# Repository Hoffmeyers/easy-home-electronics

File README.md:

This KiCad project showcases the design of a smart switch system built around the ESP32 microcontroller, aimed at enhancing automation and energy monitoring in residential or commercial settings. The system integrates both 5V and 3.3V low-dropout (LDO) voltage regulators to ensure stable power delivery to the ESP32 and associated components. An AC-DC converter is used to step down and convert mains voltage into usable DC power, making the switch compatible with standard household wiring. Additionally, the circuit incorporates voltage and current sensors to enable real-time power consumption monitoring, allowing users to track energy usage and implement protective features. The layout is optimized for compactness and reliability, with clear signal routing and robust power distribution.

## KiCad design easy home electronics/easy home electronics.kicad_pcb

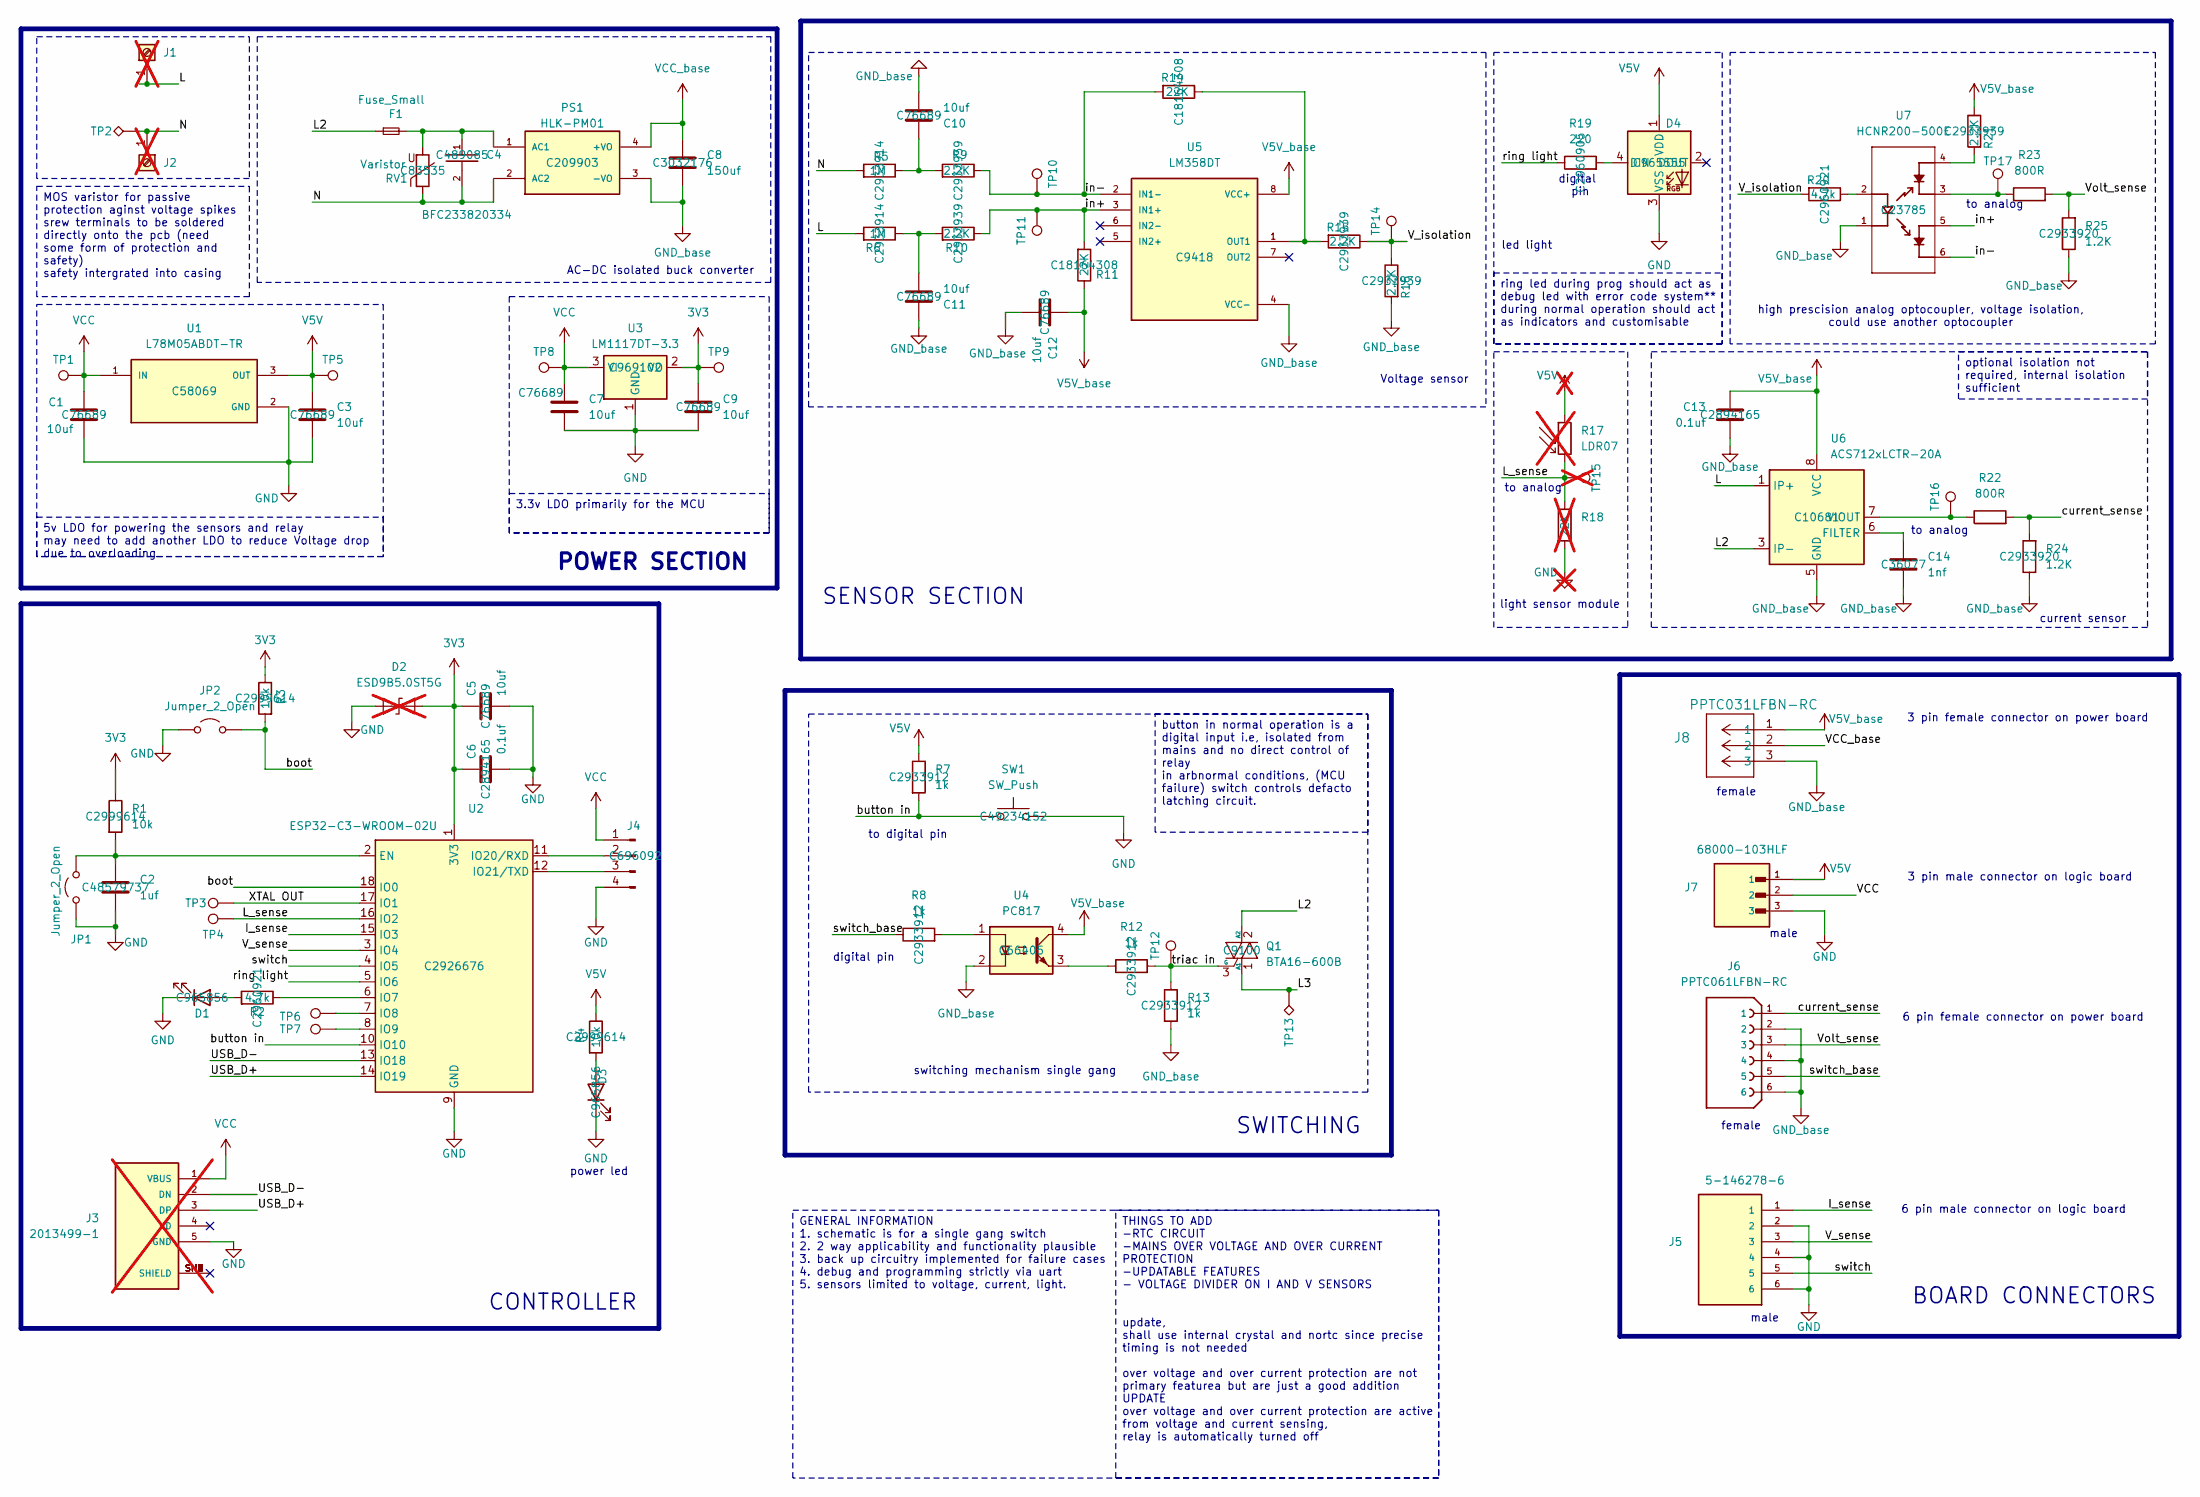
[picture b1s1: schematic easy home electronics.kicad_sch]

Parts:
C1, C3, C5, C7, C9, C10, C11, C12: 10uf; C_1812_4532Metric; LCSC PART NUMBER C76689
C2: 1uf; C_1812_4532Metric; LCSC PART NUMBER C48579737
C4: BFC233820334; CAPRR1500W80L1750T850H1500P; LCSC PART NUMBER C489085
C6, C13: 0.1uf; C_1812_4532Metric; LCSC PART NUMBER C2894165
C8: 150uf; C_Elec_6.3x7.7; LCSC PART NUMBER C3032176
C14: 1nf; C_1812_4532Metric; LCSC PART NUMBER C36077
D1, D3: LED; LED_1206_3216Metric; LCSC PART NUMBER C965856
D2: ESD9B5.0ST5G; D_SOD-923; not fitted
D4: WS2812B; LED_WS2812B_PLCC4_5.0x5.0mm_P3.2mm; LCSC PART NUMBER C965555
F1: Fuse_Small; Fuse_2512_6332Metric
J1, J2: Screw_Terminal_01x01; MountingHole_3mm_Pad_Via; not fitted
J3: 2013499-1; TE_2013499-1; PARTREV B5; not fitted
J4: Conn_01x04_Pin; Molex_PicoBlade_53261-0471_1x04-1MP_P1.25mm_Horizontal; LCSC PART NUMBER C696092
J5: 5-146278-6; TE_5-146278-6; PARTREV R
J6: PPTC061LFBN-RC; SULLINS_PPTC061LFBN-RC; PARTREV L
J7: 68000-103HLF; AMPHENOL_68000-103HLF; PARTREV DG
J8: PPTC031LFBN-RC; CONN_PPTC031_SUL
JP1, JP2: Jumper_2_Open; SolderJumper-2_P1.3mm_Open_TrianglePad1.0x1.5mm
PS1: HLK-PM01; CONV_HLK-PM01; LCSC PART NUMBER C209903
Q1: BTA16-600B; TO-220-3_Vertical; LCSC PART NUMBER C9100
R1, R3, R4: 10k; R_1812_4532Metric_Pad1.30x3.40mm_HandSolder; LCSC PART NUMBER C2999614
R2, R20: 4.7k; R_1812_4532Metric_Pad1.30x3.40mm_HandSolder; LCSC PART NUMBER C2960921
R5, R6: 1M; R_1812_4532Metric_Pad1.30x3.40mm_HandSolder; LCSC PART NUMBER C2933914
R7, R8, R12, R13: 1k; R_1812_4532Metric_Pad1.30x3.40mm_HandSolder; LCSC PART NUMBER C2933912
R9, R10, R15, R16, R21: 2.2K; R_1812_4532Metric_Pad1.30x3.40mm_HandSolder; LCSC PART NUMBER C2933939
R11, R14: 22K; R_1812_4532Metric_Pad1.30x3.40mm_HandSolder; LCSC PART NUMBER C18164308
R17: LDR07; R_LDR_5.1x4.3mm_P3.4mm_Vertical; not fitted
R18: 22K; R_1812_4532Metric_Pad1.30x3.40mm_HandSolder; not fitted
R19: 220; R_1812_4532Metric_Pad1.30x3.40mm_HandSolder; LCSC PART NUMBER C2960905
R22, R23: 800R; R_1812_4532Metric_Pad1.30x3.40mm_HandSolder
R24, R25: 1.2K; R_1812_4532Metric_Pad1.30x3.40mm_HandSolder; LCSC PART NUMBER C2933920
RV1: Varistor; RV_Disc_D12mm_W3.9mm_P7.5mm; LCSC PART NUMBER C83535
SW1: SW_Push; SW_PUSH_6mm_H5mm; LCSC PART NUMBER C49234152
TP1, TP3, TP4, TP5, TP6, TP7, TP8, TP9, TP10, TP11, TP12, TP14, TP16, TP17: TestPoint; TestPoint_Pad_D2.5mm
TP2, TP13: TestPoint_Alt; TestPoint_Pad_4.0x4.0mm
TP15: TestPoint; TestPoint_Pad_D4.0mm; not fitted
U1: L78M05ABDT-TR; VREG_L78M05ABDT-TR; PARTREV 23; LCSC PART NUMBER C58069
U2: ESP32-C3-WROOM-02U; LCSC PART NUMBER C2926676
U3: LM1117DT-3.3; TO-252-3_TabPin2; LCSC PART NUMBER C969102
U4: PC817; DIP-4_W7.62mm; LCSC PART NUMBER C66405
U5: LM358DT; SOIC127P600X175-8N; LCSC PART NUMBER C9418
U6: ACS712xLCTR-20A; SOIC-8_3.9x4.9mm_P1.27mm; LCSC PART NUMBER C10681
U7: HCNR200-500E; OPTO_HCNR200-500E; LCSC PART NUMBER C23785

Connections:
3V3: C5.1, C6.1, C9.1, D2.2 (A2), R1.1, R3.1, TP9.1, U2.1 (3V3), U3.2 (VO)
/I_sense: J5.1, U2.15 (IO3)
/L: J1.1, R6.2, U6.1 (IP+), U6.2 (IP+)
/L2: F1.1, Q1.2 (A2), U6.3 (IP-), U6.4 (IP-)
/L3: Q1.1 (A1), TP13.1
/L_sense: R17.2, R18.1, TP4.1, TP15.1, U2.16 (IO2)
/N: C4.2, J2.1, PS1.2 (AC2), R5.2, RV1.1, TP2.1
/USB_D+: J3.3 (DP), U2.14 (IO19)
/USB_D-: J3.2 (DN), U2.13 (IO18)
/V_isolation: R15.1, R16.1, R20.2, TP14.1
/V_sense: J5.3, U2.3 (IO4)
/Volt_sense: J6.3, R23.2, R25.2
/XTAL OUT: TP3.1, U2.17 (IO1)
/boot: JP2.2 (B), R3.2, U2.18 (IO0)
/button in: R7.2, SW1.1, U2.10 (IO10)
/current_sense: J6.1, R22.2, R24.2
/in+: R10.1, R11.2, TP11.1, U5.3 (IN1+), U7.5
/in-: R9.1, R14.2, TP10.1, U5.2 (IN1-), U7.6
/ring light: R19.1, U2.5 (IO6)
/switch: J5.5, U2.4 (IO5)
/switch_base: J6.5, R8.1
/triac in: Q1.3 (G), R12.2, R13.1, TP12.1
GND: C1.2, C2.2, C3.2, C5.2, C6.2, C7.2, C9.2, D1.1 (K), D2.1 (A1), D3.1 (K), D4.3 (VSS), J3.5 (GND), J4.4, J5.2, J5.4, J5.6, J7.3, JP1.1 (A), JP2.1 (A), R18.2, SW1.2, U1.2 (GND), U2.9 (GND), U2.19 (GND), U3.1 (GND)
GND_base: C8.2, C10.2, C11.1, C12.2, C13.2, C14.2, J6.2, J6.4, J6.6, J8.3, PS1.3 (-VO), R13.2, R16.2, R24.1, R25.1, U4.2, U5.4 (VCC-), U6.5 (GND), U7.1
unnamed: C10.1, R5.1, R9.2
unnamed: C11.2, R6.1, R10.2
unnamed: D1.2 (A), R2.2
unnamed: D3.2 (A), R4.2
unnamed: D4.4 (DIN), R19.2
unnamed: J4.2, U2.11 (IO20/RXD)
unnamed: J4.3, U2.12 (IO21/TXD)
unnamed: C2.1, JP1.2 (B), R1.2, U2.2 (EN)
unnamed: C4.1, F1.2, PS1.1 (AC1), RV1.2
unnamed: R8.2, U4.1
unnamed: R12.1, U4.3
unnamed: R20.1, U7.2
unnamed: R21.2, U7.4
unnamed: R23.1, TP17.1, U7.3
unnamed: R2.1, U2.6 (IO7)
unnamed: TP6.1, U2.7 (IO8)
unnamed: TP7.1, U2.8 (IO9)
unnamed: R14.1, R15.2, U5.1 (OUT1)
unnamed: C14.1, U6.6 (FILTER)
unnamed: R22.1, TP16.1, U6.7 (VIOUT)
V5V: C3.1, D4.1 (VDD), J7.1, R4.1, R7.1, R17.1, TP5.1, U1.3 (OUT)
V5V_base: C12.1, C13.1, J8.1, R11.1, R21.1, U4.4, U5.8 (VCC+), U6.8 (VCC)
VCC: C1.1, C7.1, J3.1 (VBUS), J4.1, J7.2, TP1.1, TP8.1, U1.1 (IN), U3.3 (VI)
VCC_base: C8.1, J8.2, PS1.4 (+VO)

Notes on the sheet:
power led
high prescision analog optocoupler, voltage isolation, could use another optocoupler
led light
current sensor
3 pin male connector on logic board
light sensor module
male
to analog
SENSOR SECTION
digital pin
3 pin female connector on power board
CONTROLLER
BOARD CONNECTORS
SWITCHING
switching mechanism single gang
Voltage sensor
digital pin
6 pin male connector on logic board
female
to digital pin
6 pin female connector on power board
AC-DC isolated buck converter
POWER SECTION
optional isolation not required, internal isolation sufficient
THINGS TO ADD -RTC CIRCUIT -MAINS OVER VOLTAGE AND OVER CURRENT PROTECTION -UPDATABLE FEATURES - VOLTAGE DIVIDER ON I AND V SENSORS update, shall use internal crystal and nortc since precise timing is not needed over voltage and over current protection are not primary featurea but are just a good a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
MOS varistor for passive protection aginst voltage spikes srew terminals to be soldered directly onto the pcb (need some form of protection and safety) safety intergrated into casing
GENERAL INFORMATION 1. schematic is for a single gang switch 2. 2 way applicability and functionality plausible 3. back up circuitry implemented for failure cases 4. debug and programming strictly via uart 5. sensors limited to voltage, current, light.
3.3v LDO primarily for the MCU
button in normal operation is a digital input i.e, isolated from mains and no direct control of relay in arbnormal conditions, (MCU failure) switch controls defacto latching circuit.
ring led during prog should act as debug led with error code system** during normal operation should act as indicators and customisable
5v LDO for powering the sensors and relay may need to add another LDO to reduce Voltage drop due to overloading

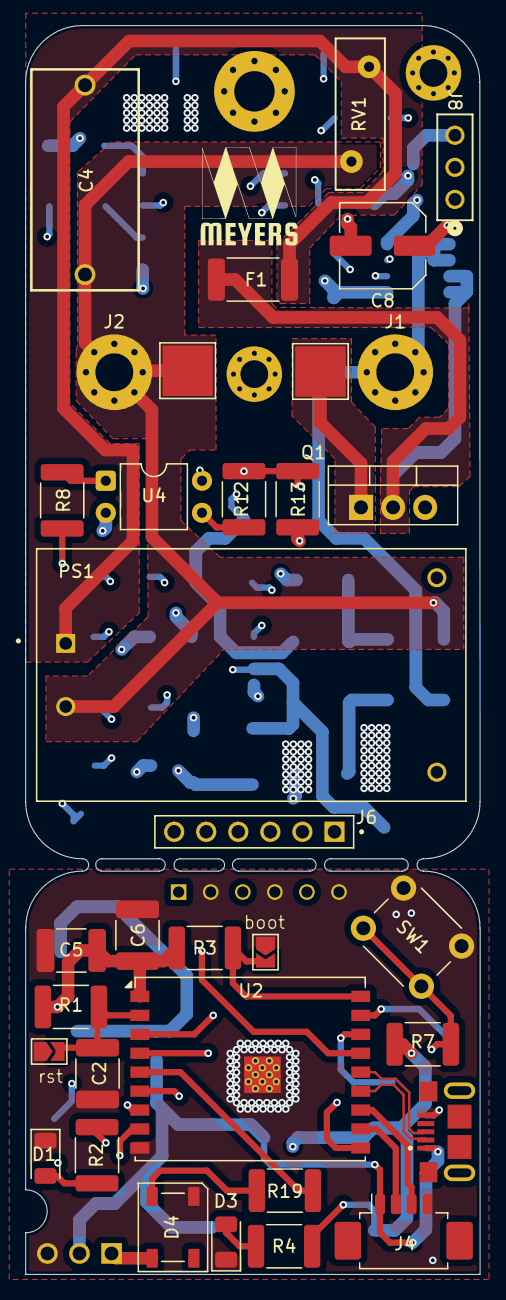
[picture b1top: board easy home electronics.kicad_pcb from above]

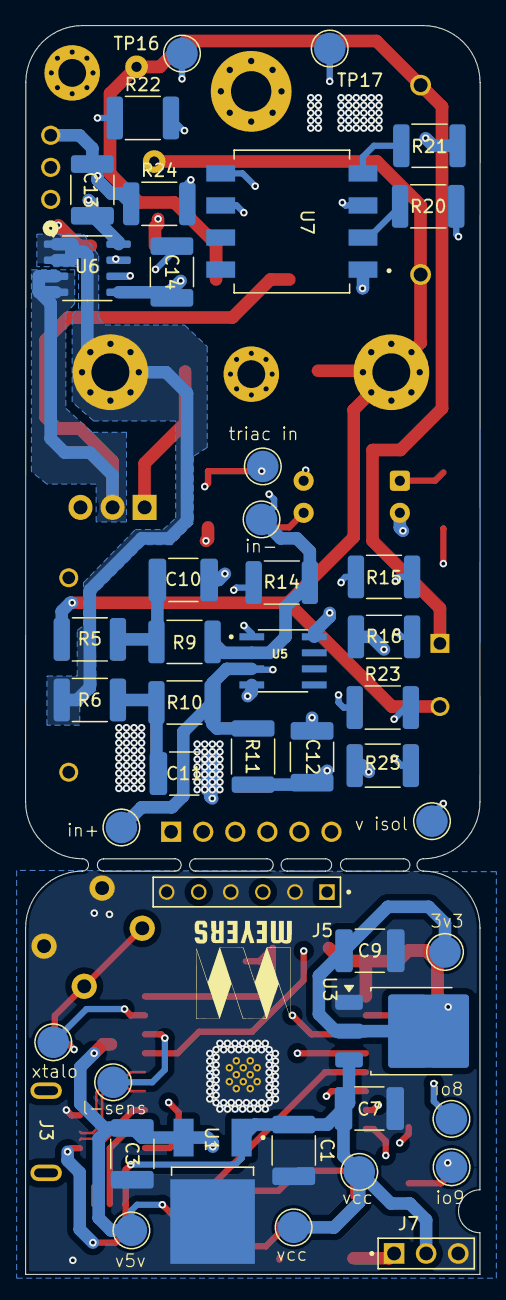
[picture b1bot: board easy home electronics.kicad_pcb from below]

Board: 4 copper layers, 36.0 x 98.9 mm, 78 parts (44 on the bottom side), 48 nets.

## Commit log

2025-07-08 Add files via upload
    new design backup
2025-09-15 commit 1.0.1
